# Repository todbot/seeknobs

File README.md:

# seeknobs

knob board for seesaw, and also a drone synth

seeknobs PCB features:

- 8 knobs, read by seesaw
- 4 buttons, read by seesaw
- 8 NeoPixels, driven by seesaw
- 1 TRS 3.5mm (1/8") output as either audio or MIDI, driven by QTPy
- socket for optional QTPy M0 or RP2040 

Demo videos:

https://user-images.githubusercontent.com/274093/187097590-4c935e73-8458-4f9c-81a5-5cf9e1a02f47.mp4

https://user-images.githubusercontent.com/274093/166125135-3420fb34-c7c5-4f65-addc-f08b40fc5832.mp4

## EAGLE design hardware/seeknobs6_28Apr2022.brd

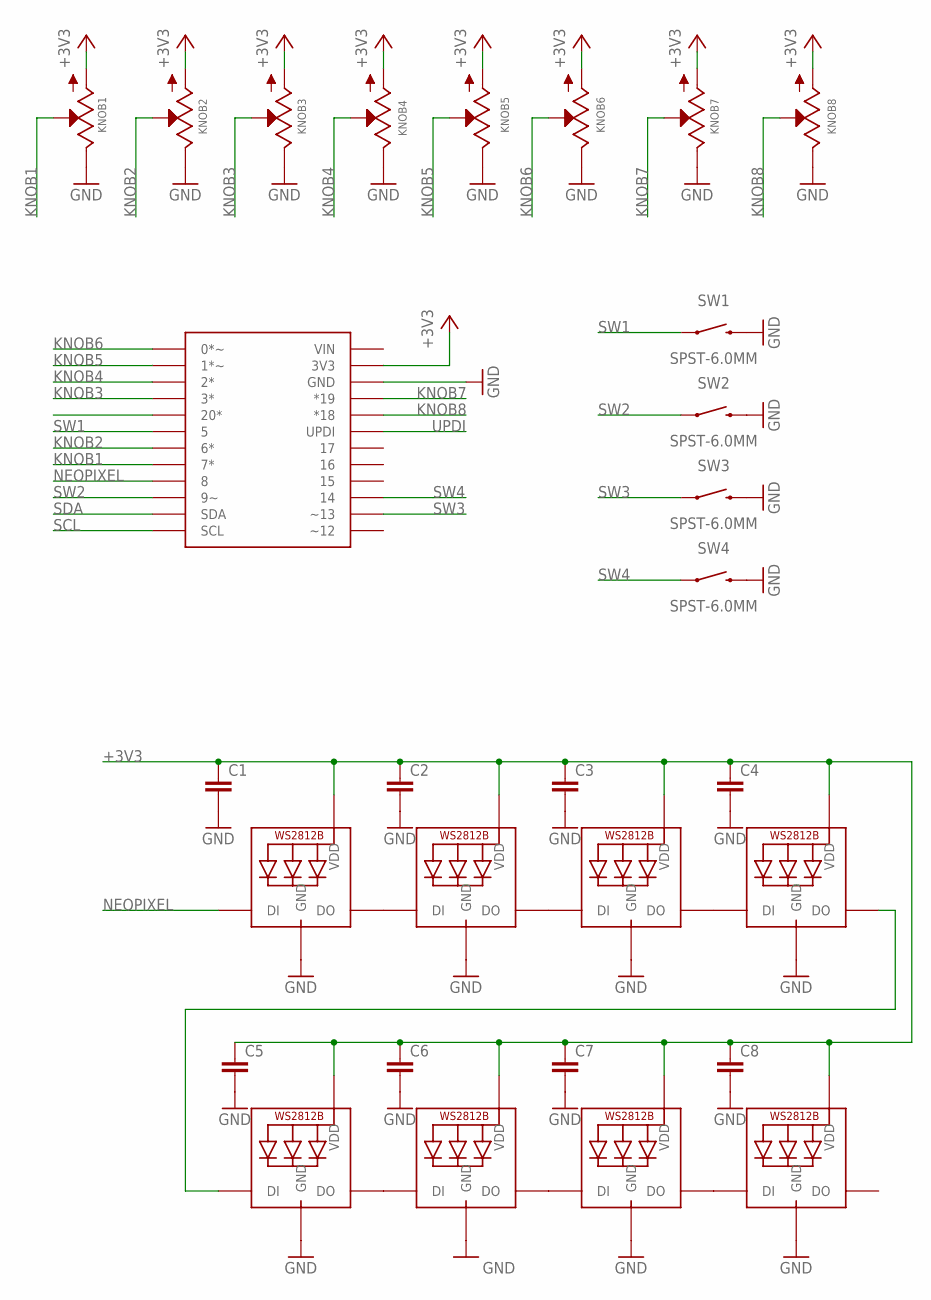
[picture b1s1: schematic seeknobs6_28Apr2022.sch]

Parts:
C1, C2, C3, C4, C5, C6, C7, C8: C-EUC0805; C0805
KNOB1, KNOB2, KNOB3, KNOB4, KNOB5, KNOB6, KNOB7, KNOB8: POT; ALPS_POT
LED1, LED2, LED3, LED4, LED5, LED6, LED7, LED8: WS2812B5050EZ; WS2812B-EASY
SEESAW: ADAFRUIT_SEESAW_ATTINY817
SW1, SW2, SW3, SW4: SPST-6.0MM; TACTILE_SWITCH_PTH_6.0MM

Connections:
+3V3: C1.1, C2.1, C3.1, C4.1, C5.1, C6.1, C7.1, C8.1, KNOB1.P$3 (A), KNOB2.P$3 (A), KNOB3.P$3 (A), KNOB4.P$3 (A), KNOB5.P$3 (A), KNOB6.P$3 (A), KNOB7.P$3 (A), KNOB8.P$3 (A), LED1.1-VDD (VDD), LED2.1-VDD (VDD), LED3.1-VDD (VDD), LED4.1-VDD (VDD), LED5.1-VDD (VDD), LED6.1-VDD (VDD), LED7.1-VDD (VDD), LED8.1-VDD (VDD), SEESAW.P23 (3V3)
GND: C1.2, C2.2, C3.2, C4.2, C5.2, C6.2, C7.2, C8.2, KNOB1.P$1 (E), KNOB2.P$1 (E), KNOB3.P$1 (E), KNOB4.P$1 (E), KNOB5.P$1 (E), KNOB6.P$1 (E), KNOB7.P$1 (E), KNOB8.P$1 (E), LED1.3-GND (GND), LED2.3-GND (GND), LED3.3-GND (GND), LED4.3-GND (GND), LED5.3-GND (GND), LED6.3-GND (GND), LED7.3-GND (GND), LED8.3-GND (GND), SEESAW.P22 (GND), SW1.3 (2), SW2.3 (2), SW3.3 (2), SW4.3 (2)
KNOB1: KNOB1.P$2 (S), SEESAW.P8 (7*)
KNOB2: KNOB2.P$2 (S), SEESAW.P7 (6*)
KNOB3: KNOB3.P$2 (S), SEESAW.P4 (3*)
KNOB4: KNOB4.P$2 (S), SEESAW.P3 (2*)
KNOB5: KNOB5.P$2 (S), SEESAW.P2 (1*~)
KNOB6: KNOB6.P$2 (S), SEESAW.0 (0*~)
KNOB7: KNOB7.P$2 (S), SEESAW.P21 (*19)
KNOB8: KNOB8.P$2 (S), SEESAW.P20 (*18)
unnamed: LED2.2-DOUT (DO), LED3.4-DIN (DI)
unnamed: LED3.2-DOUT (DO), LED4.4-DIN (DI)
unnamed: LED1.2-DOUT (DO), LED2.4-DIN (DI)
unnamed: LED5.2-DOUT (DO), LED6.4-DIN (DI)
unnamed: LED6.2-DOUT (DO), LED7.4-DIN (DI)
unnamed: LED7.2-DOUT (DO), LED8.4-DIN (DI)
unnamed: LED4.2-DOUT (DO), LED5.4-DIN (DI)
NEOPIXEL: LED1.4-DIN (DI), SEESAW.P9 (8)
SCL: SEESAW.P12 (SCL)
SDA: SEESAW.P11 (SDA)
SW1: SEESAW.P6 (5), SW1.1
SW2: SEESAW.P10 (9~), SW2.1
SW3: SEESAW.P14 (~13), SW3.1
SW4: SEESAW.P15 (14), SW4.1
UPDI: SEESAW.P19 (UPDI)

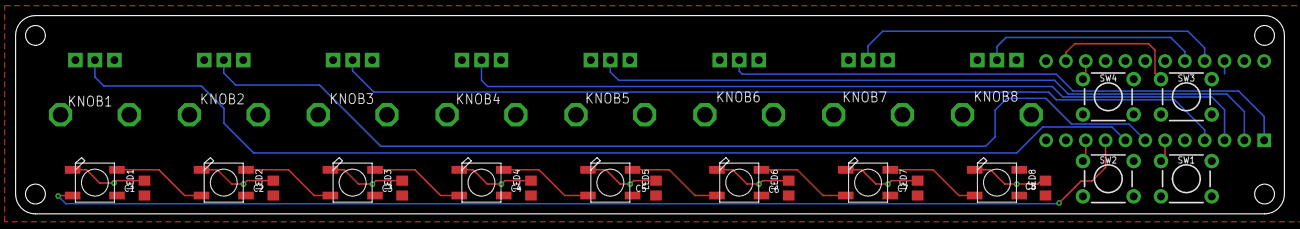
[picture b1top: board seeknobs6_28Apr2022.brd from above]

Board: 2 copper layers, 162.6 x 25.4 mm, 29 parts (1 on the bottom side), 22 nets.

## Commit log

2022-02-17 finally in git
2022-02-17 arduino sketch cleanup
2022-02-17 more playing
2022-02-18 make drone sketch multi platform (SAMD21 and RP2040)
2022-02-18 works on SAMD21 nicely it seems
2022-02-18 some buttons do things
2022-02-18 okay this is fun
2022-02-18 readme update
2022-02-18 omg this one sounds so cool when set to huge chord and flutter button pressed
2022-02-21 nice
2022-02-23 new day, new layout
2022-02-23 more pcb
2022-02-23 front panel design
2022-02-24 added front silk to 22Feb2022
2022-04-28 non-qtpy version
2022-04-29 qtpy_knob_test
2022-04-30 doc updates, cirpy example
2022-04-30 added demo movie
2022-04-30 small fixes to cirpy demo speeds things up to 6ms per loop
2022-04-30 about as usable as I can make CiruitPython demo for now: 5-7ms per loop
2022-04-30 cirpy bitmask formatting fix
2022-04-30 simple knobs to midi example
2022-04-30 a little filtering for CircuitPython knobs_midi.py

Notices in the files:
parts and their libraries:
SparkFun-Switches: Licensing: Creative Commons ShareAlike 4.0 International - https://creativecommons.org/licenses/by-sa/4.0
